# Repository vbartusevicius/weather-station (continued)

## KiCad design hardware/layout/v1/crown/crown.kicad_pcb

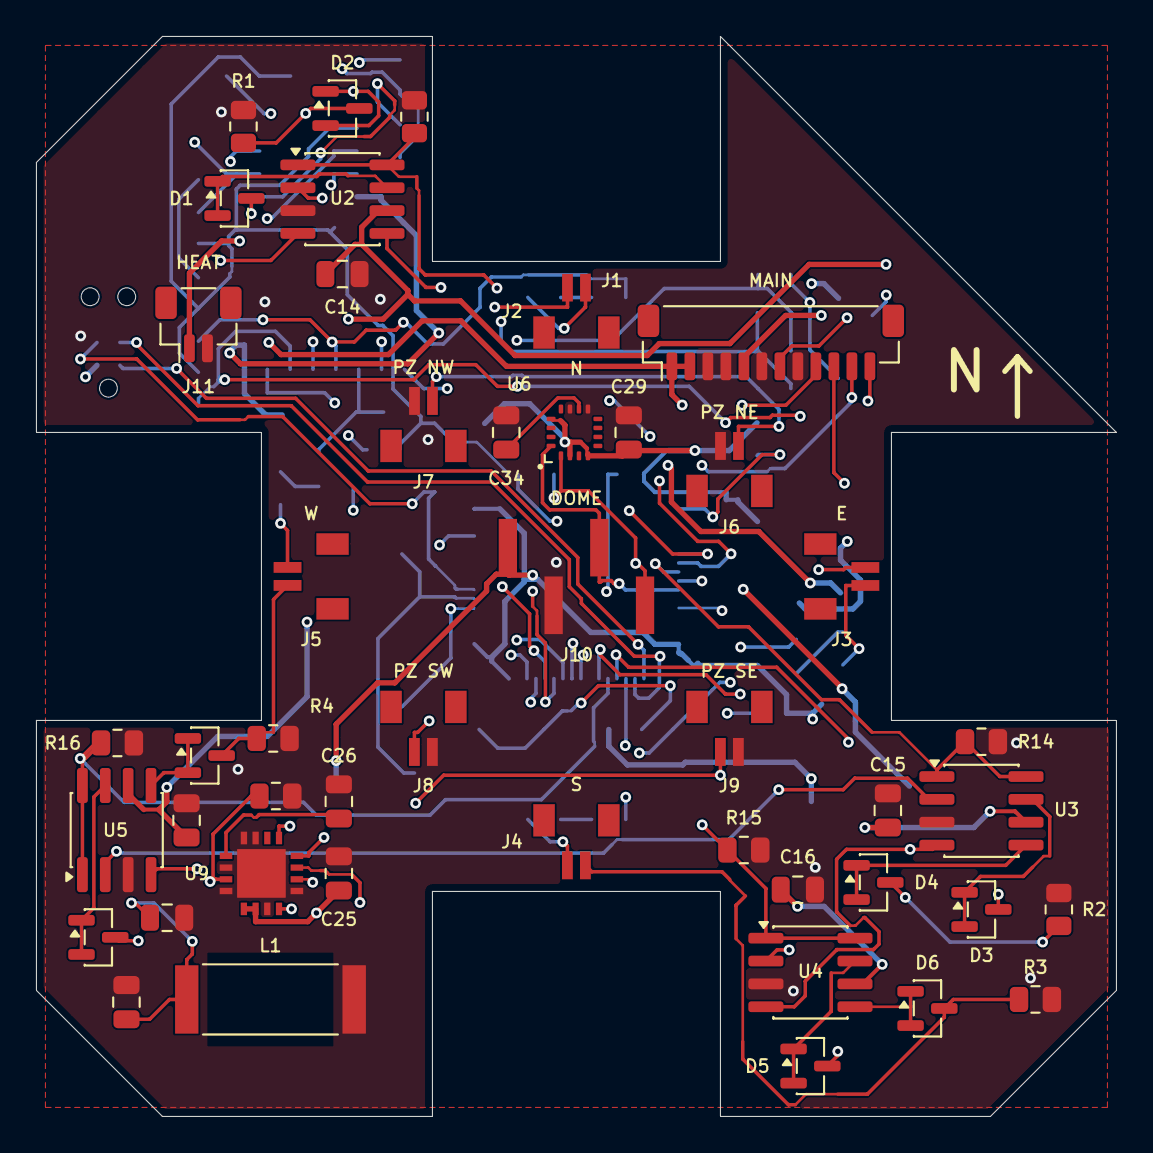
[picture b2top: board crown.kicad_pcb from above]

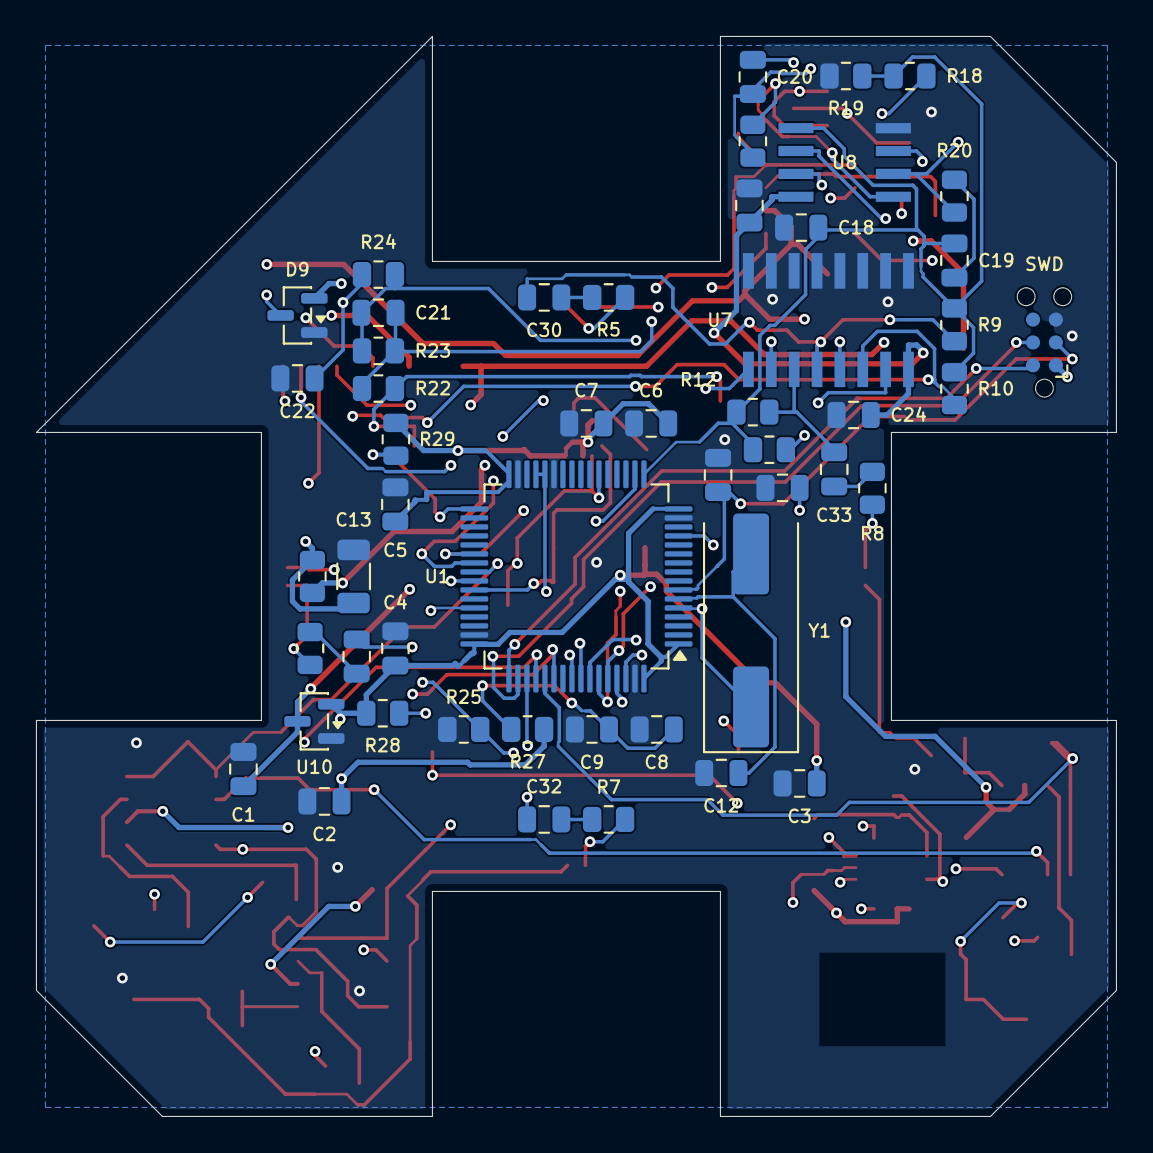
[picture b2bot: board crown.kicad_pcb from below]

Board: 4 copper layers, 60.0 x 60.0 mm, 96 parts (51 on the bottom side), 66 nets.

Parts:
C1, C8, C14, C15, C16, C17, C18, C25, C26: 1u 50V; C_0805_2012Metric
C2, C7, C34: 10u 10V; C_0805_2012Metric
C3, C4, C5, C6, C9, C10, C19, C23, C24, C29: 100n 50V; C_0805_2012Metric
C11, C12: 33p C0G 50V; C_0805_2012Metric
C13: 22u 25V; C_1206_3216Metric
C20: 220p C0G 50V; C_0805_2012Metric
C21: 22n 50V; C_0805_2012Metric
C22: 1n 50V; C_0805_2012Metric
C27, C28: 470p C0G 50V; C_0805_2012Metric
C30, C31, C32, C33: 10n 50V; C_0805_2012Metric
D1, D2, D3, D4, D5, D6, D7, D8, D9: BAV99; SOT-23
J1: Main board; JST_SH_BM12B-SRSS-TB_1x12-1MP_P1.00mm_Vertical
J2: XD_N; JST_BM02B-SRSS-TB
J3: XD_E; JST_BM02B-SRSS-TB
J4: XD_S; JST_BM02B-SRSS-TB
J5: XD_W; JST_BM02B-SRSS-TB
J6: PIEZO_NE; JST_BM02B-SRSS-TB
J7: PIEZO_NW; JST_BM02B-SRSS-TB
J8: PIEZO_SW; JST_BM02B-SRSS-TB
J9: PIEZO_SE; JST_BM02B-SRSS-TB
J10: DOME_SOCKET; HX_PZ2.54-1x4P-SMD
J11: AUX 12V_HEAT; JST_SH_BM02B-SRSS-TB_1x02-1MP_P1.00mm_Vertical
J12: SWD; Tag-Connect_TC2030-IDC-NL_2x03_P1.27mm_Vertical
L1: 100uH; AS3935_Antenna_MA5532_SDTR1103
R1, R2, R3, R4: 330R; R_0805_2012Metric
R5, R6, R7, R8: 47k; R_0805_2012Metric
R9, R10, R11, R12: 1M; R_0805_2012Metric
R13, R14, R15, R16: 4k7; R_0805_2012Metric
R17, R27: 10R; R_0805_2012Metric
R18, R19, R25, R26, R28, R29: 10k; R_0805_2012Metric
R20, R22: 1k; R_0805_2012Metric
R21: 6k8; R_0805_2012Metric
R23: 4M7; R_0805_2012Metric
R24: 22k; R_0805_2012Metric
U1: STM32G431RBT6; LQFP-64_10x10mm_P0.5mm
U2, U3, U4, U5: UCC27524ADR; SOIC-8_3.9x4.9mm_P1.27mm
U6: MMC5983MA; MEMSIC_MMC5983MA_LGA-16
U7: 74HC4052D; TI_CD4052BM96_SOIC-16
U8: TLV9062IDR; TI_TLV9062IDR_SOIC-8
U9: AS3935-BQFT; ScioSense_AS3935_QFN-16
U10: XC6206P332MR; SOT-23
Y1: 8MHz; Crystal_SMD_HC49-SD

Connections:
+3V3: C2.1, C3.1, C4.1, C5.1, C6.1, C7.1, C23.1, C24.1, C25.1, C29.1, D9.2, J10.1, J12.1, R27.1, R28.2, R29.2, U1.1, U1.16, U1.32, U1.48, U1.64, U6.2, U6.4, U6.13, U7.16, U8.8, U9.5, U9.6, U10.2
+3V3A: C8.1, C9.1, R18.1, R27.2, U1.28, U1.29
+5V: C1.1, J1.5, U10.3
+12V_HEAT: J1.1, J1.2, J11.1, R17.1
AS_ACG: C26.1, U9.1
AS_CS: U1.51, U9.8
AS_INP: C27.1, C28.1, L1.1, R26.1, U9.3
AS_IRQ: U1.62, U9.10
AS_MISO: U1.57, U9.12
AS_MOSI: U1.58, U9.13
AS_SCK: U1.56, U9.11
BL_PA10: R28.1, U1.44
BL_PB12: R29.1, U1.33
CROWN_BOOT0: J1.12, R25.1, U1.61
CROWN_IRQ: J1.10, U1.54
CROWN_NRST: C10.1, J1.11, J12.3, U1.7
GND: C1.2, C2.2, C3.2, C4.2, C5.2, C6.2, C7.2, C8.2, C9.2, C10.2, C11.2, C12.2, C13.2, C14.2, C15.2, C16.2, C17.2, C18.2, C22.2, C23.2, C24.2, C25.2, C26.2, C27.2, C28.2, C29.2, C34.2, D9.1, J1.3, J1.4, J1.6, J1.8, J6.2, J7.2, J8.2, J9.2, J10.2, J11.2, J12.5, L1.2, R1.2, R2.2, R3.2, R4.2, R13.2, R14.2, R15.2, R16.2, R19.2, R25.2, R26.2, U1.15, U1.27, U1.31, U1.47, U1.63, U2.3, U3.3, U4.3, U5.3, U6.9, U6.11, U7.1, U7.2, U7.3, U7.4, U7.5, U7.6, U7.7, U7.8, U8.4, U9.2, U9.4, U9.7, U9.9, U9.15, U9.16, U9.17, U10.1
I2C_SCL: J1.9, J10.4, U1.22, U6.1
I2C_SDA: J1.7, J10.3, U1.42, U6.16
MAG_CAP: C34.1, U6.10
MUX_S0: U1.59, U7.10
MUX_S1: U1.60, U7.9
PIEZO_IN: D9.3, J6.1, J7.1, J8.1, J9.1, R22.1
PIEZO_INV: C21.1, R22.2, R23.1, U8.6
PIEZO_OUT: C21.2, R23.2, R24.1, U8.7
RAIN_ADC: C22.1, R24.2, U1.18
SWCLK: J12.4, U1.50
SWDIO: J12.2, U1.49
TX_N: U1.52, U2.4, U3.4, U4.4, U5.4
TX_P: U1.38, U2.2, U3.2, U4.2, U5.2
US_AMP_FB: C20.1, R20.1, R21.1, U8.2
US_AMP_G: C19.1, R20.2
US_AMP_OUT: C20.2, R21.2, U1.13, U8.1
US_RX_MUX: U7.13, U8.3
US_VREF: C18.1, C19.2, R9.2, R10.2, R11.2, R12.2, R18.2, R19.1, U1.17, U8.5
VDRV: C13.1, C14.1, C15.1, C16.1, C17.1, R17.2, U2.6, U3.6, U4.6, U5.6
XD_EN_E: R14.1, U1.40, U3.1, U3.8
XD_EN_N: R13.1, U1.39, U2.1, U2.8
XD_EN_S: R15.1, U1.41, U4.1, U4.8
XD_EN_W: R16.1, U1.53, U5.1, U5.8
XD_E_A: D3.3, J3.1, R6.1
XD_E_B: D4.3, J3.2, R2.1
XD_E_OUT_A: D3.1, D3.2, U3.7
XD_E_OUT_B: D4.1, D4.2, U3.5
XD_E_RX: C31.2, R10.1, U7.14
XD_E_RXC: C31.1, R6.2
XD_N_A: D1.3, J2.1, R5.1
XD_N_B: D2.3, J2.2, R1.1
XD_N_OUT_A: D1.1, D1.2, U2.7
XD_N_OUT_B: D2.1, D2.2, U2.5
XD_N_RX: C30.2, R9.1, U7.12
XD_N_RXC: C30.1, R5.2
XD_S_A: D5.3, J4.1, R7.1
XD_S_B: D6.3, J4.2, R3.1
XD_S_OUT_A: D5.1, D5.2, U4.7
XD_S_OUT_B: D6.1, D6.2, U4.5
XD_S_RX: C32.2, R11.1, U7.15
XD_S_RXC: C32.1, R7.2
XD_W_A: D7.3, J5.1, R8.1
XD_W_B: D8.3, J5.2, R4.1
XD_W_OUT_A: D7.1, D7.2, U5.7
XD_W_OUT_B: D8.1, D8.2, U5.5
XD_W_RX: C33.2, R12.1, U7.11
XD_W_RXC: C33.1, R8.2
XTAL_IN: C11.1, U1.5, Y1.1
XTAL_OUT: C12.1, U1.6, Y1.2

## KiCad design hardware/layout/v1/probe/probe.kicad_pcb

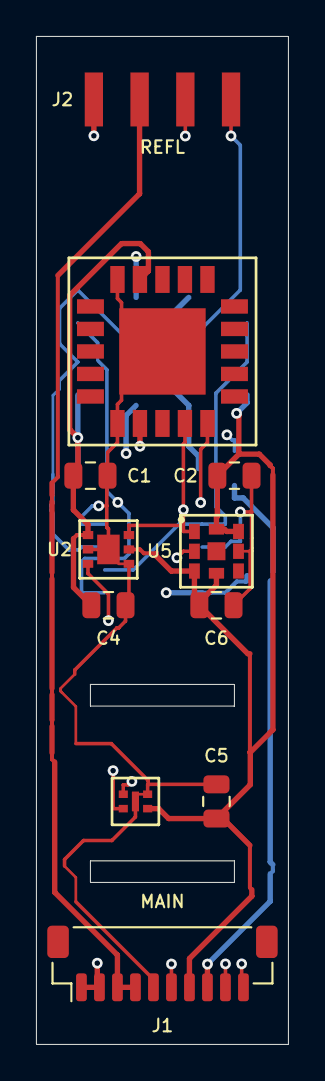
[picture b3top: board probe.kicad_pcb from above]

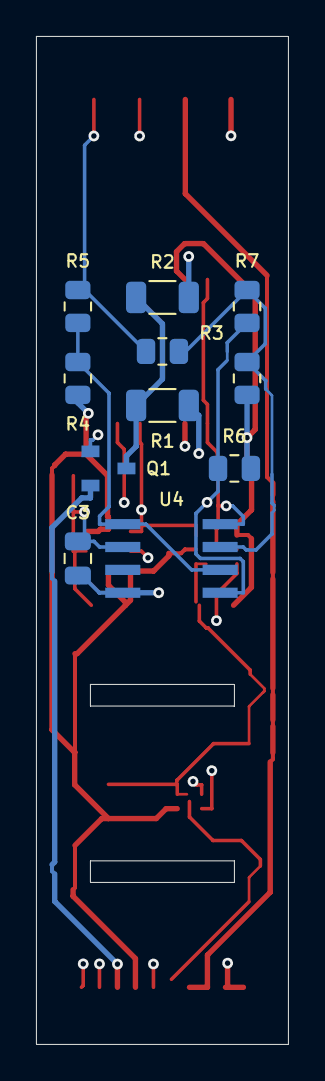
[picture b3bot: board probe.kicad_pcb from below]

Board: 4 copper layers, 14.0 x 56.0 mm, 22 parts (11 on the bottom side), 12 nets.

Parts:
C1: 10u 10V; C_0805_2012Metric
C2, C3, C4, C5, C6: 100n 50V; C_0805_2012Metric
J1: Main board; JST_SH_BM10B-SRSS-TB_1x10-1MP_P1.00mm_Vertical
J2: Reflector T-Socket SMD; HX_PM2.54-1x4P-RA-SMD
Q1: AO3400A; AOS_AO3400A_SOT-23
R1, R2: 680R; R_1206_3216Metric
R3, R4, R6: 10k; R_0805_2012Metric
R5: 51k; R_0805_2012Metric
R7: 470k; R_0805_2012Metric
TH1: 10k NTC; R_0805_2012Metric
U1: SCD41-D-R2; Sensirion_SCD41_LGA-20
U2: SGP41-D-R4; Sensirion_SGP41_DFN-6
U3: SHT40-AD1F-R2; Sensirion_SHT45_DFN-4
U4: LM2903DR2G; ON_LM393DR2G_SOIC-8
U5: BMP585; Bosch_BMP585_LGA-9

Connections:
+3V3_PROBE: C1.1, C2.1, C4.1, C5.1, C6.1, J1.7, R3.1, R4.1, R6.1, U1.7, U1.19, U2.1, U2.5, U3.3, U5.3, U5.4, U5.7, U5.8
+12V_HEAT: C3.1, J1.1, J1.2, J2.1, R1.1, R2.1, U4.8
CO2_GATE: Q1.1, R6.2, R7.1, U4.1
CO2_HEAT_RTN: J1.8, Q1.2
CO2_HEAT_SW: Q1.3, R1.2, R2.2
CO2_NTC: R3.2, R7.2, TH1.1, U4.3
CO2_VSET: R4.2, R5.1, U4.2, U4.5
GND: C1.2, C2.2, C3.2, C4.2, C5.2, C6.2, J1.5, J2.4, R5.2, TH1.2, U1.6, U1.20, U1.21, U2.2, U2.4, U2.7, U3.4, U3.5, U4.4, U4.6, U5.6
HEAT_SW: J1.3, J1.4, J2.2
I2C_SCL: J1.10, U1.9, U2.6, U3.2, U5.1
I2C_SDA: J1.9, U1.10, U2.3, U3.1, U5.2
NTC_SENSE: J1.6, J2.3

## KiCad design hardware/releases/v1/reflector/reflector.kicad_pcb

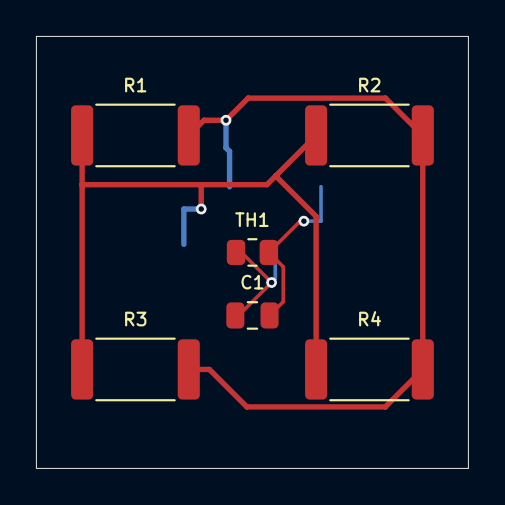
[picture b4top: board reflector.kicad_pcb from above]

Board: 4 copper layers, 24.0 x 24.0 mm, 7 parts (1 on the bottom side), 4 nets.

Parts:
C1: 100n 50V; C_0805_2012Metric
J1: Probe T-Header SMD; HX_PZ2.54-1x4P-SMD
R1, R2, R3, R4: 120R; R_2512_6332Metric
TH1: 10k NTC; R_0805_2012Metric

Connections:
+12V_HEAT: J1.1, R1.1, R2.1, R3.1, R4.1
GND: C1.2, J1.4, TH1.2
HEAT_SW: J1.2, R1.2, R2.2, R3.2, R4.2
NTC_SENSE: C1.1, J1.3, TH1.1

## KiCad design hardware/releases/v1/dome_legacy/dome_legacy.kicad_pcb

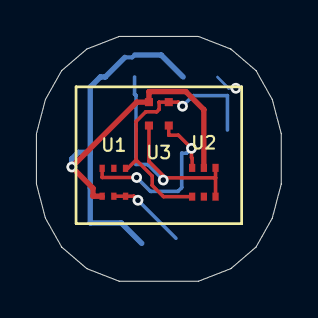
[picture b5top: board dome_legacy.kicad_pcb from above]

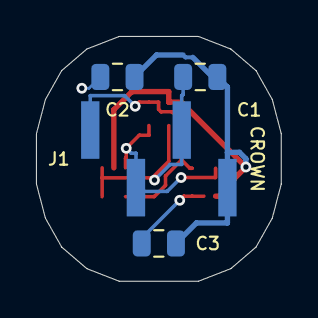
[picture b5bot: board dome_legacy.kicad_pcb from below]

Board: 4 copper layers, 13.6 x 13.6 mm, 7 parts (4 on the bottom side), 4 nets.

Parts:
C1, C2: 100n 50V; C_0805_2012Metric
C3: 1u 50V; C_0805_2012Metric
J1: CROWN_RISER; HX_PZ2.54-1x4P-SMD
U1: LTR-390UV-01; LiteOn_LTR-390UV-01
U2: TSL25911FN; AMS_TSL25911FN
U3: GUVB-C31SM; GenUV_GUVB-C31SM

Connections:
+3V3: C1.1, C2.1, C3.1, J1.1, U1.1, U2.5, U3.4
GND: C1.2, C2.2, C3.2, J1.2, U1.2, U1.3, U2.3, U2.4, U3.1
I2C_SCL: J1.4, U1.4, U2.1, U3.3
I2C_SDA: J1.3, U1.6, U2.6, U3.2

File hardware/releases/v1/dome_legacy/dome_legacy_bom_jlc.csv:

Comment,Designator,Footprint,LCSC Part #
100n 50V,"C1,C2",C_0805_2012Metric,C49678
1u 50V,C3,C_0805_2012Metric,C28323
CROWN_RISER,J1,HX_PZ2.54-1x4P-SMD,C41417361
LTR-390UV-01,U1,LiteOn_LTR-390UV-01,C492374
TSL25911FN,U2,AMS_TSL25911FN,C176812

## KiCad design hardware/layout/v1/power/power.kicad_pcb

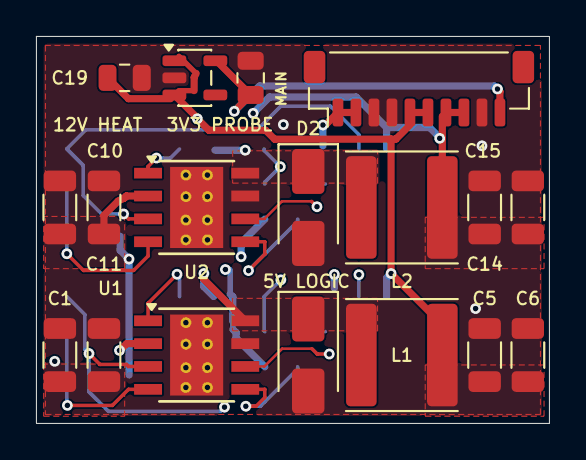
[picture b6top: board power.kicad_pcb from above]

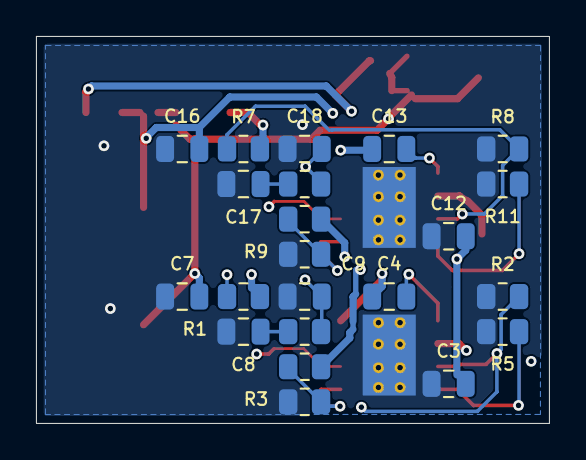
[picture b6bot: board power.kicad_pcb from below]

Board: 4 copper layers, 28.5 x 21.5 mm, 40 parts (22 on the bottom side), 19 nets.

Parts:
C1, C2, C10, C11: 2u2 100V; C_1206_3216Metric
C3, C12: 100n 100V; C_0805_2012Metric
C4, C7, C13, C16: 100n 50V; C_0805_2012Metric
C5, C6: 47u 10V; C_1206_3216Metric
C8: 33n 50V; C_0805_2012Metric
C9, C18: 68p C0G 50V; C_0805_2012Metric
C14, C15: 22u 25V; C_1206_3216Metric
C17: 18n 50V; C_0805_2012Metric
C19: 1u 50V; C_0805_2012Metric
C20: 10u 10V; C_0805_2012Metric
D1, D2: B360A; D_SMA
J1: Main board; JST_SH_BM10B-SRSS-TB_1x10-1MP_P1.00mm_Vertical
L1: 8.2uH; L_Sunlord_SWPA6045S
L2: 22uH; L_Sunlord_SWPA6045S
R1, R7: 511k; R_0805_2012Metric
R2, R8: 82k5; R_0805_2012Metric
R3: 53k6; R_0805_2012Metric
R4: 10k2; R_0805_2012Metric
R5, R11: 130k; R_0805_2012Metric
R6, R12: 6k49; R_0805_2012Metric
R9: 140k; R_0805_2012Metric
R10: 10k; R_0805_2012Metric
U1, U2: TPS54360DDAR; TI_SO-PowerPAD-8_ThermalVias
U3: AP2112K-3.3; SOT-23-5

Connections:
+3V3_PROBE: C20.1, J1.10, U3.5
+5V: C5.1, C6.1, C7.1, C19.1, J1.5, J1.6, L1.2, R3.1, U3.1, U3.3
+12V_HEAT: C14.1, C15.1, C16.1, J1.7, J1.8, L2.2, R9.1
GND: C1.2, C2.2, C3.2, C5.2, C6.2, C7.2, C8.2, C9.2, C10.2, C11.2, C12.2, C14.2, C15.2, C16.2, C17.2, C18.2, C19.2, C20.2, D1.2, D2.2, J1.3, J1.4, J1.9, R2.2, R4.2, R5.2, R8.2, R10.2, R11.2, U1.7, U1.9, U2.7, U2.9, U3.2
HEAT_BST: C13.1, U2.1
HEAT_CC: C17.1, R12.2
HEAT_COMP: C18.1, R12.1, U2.6
HEAT_EN: R7.2, R8.1, U2.3
HEAT_FB: R9.2, R10.1, U2.5
HEAT_RT: R11.1, U2.4
HEAT_SW: C13.2, D2.1, L2.1, U2.8
LOGIC_BST: C4.1, U1.1
LOGIC_CC: C8.1, R6.2
LOGIC_COMP: C9.1, R6.1, U1.6
LOGIC_EN: R1.2, R2.1, U1.3
LOGIC_FB: R3.2, R4.1, U1.5
LOGIC_RT: R5.1, U1.4
LOGIC_SW: C4.2, D1.1, L1.1, U1.8
VIN_PROT: C1.1, C2.1, C3.1, C10.1, C11.1, C12.1, J1.1, J1.2, R1.1, R7.1, U1.2, U2.2

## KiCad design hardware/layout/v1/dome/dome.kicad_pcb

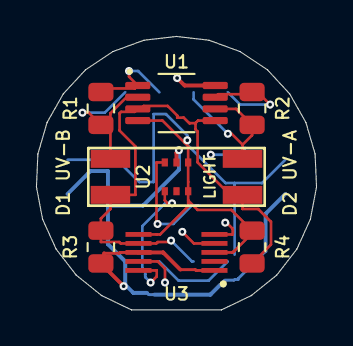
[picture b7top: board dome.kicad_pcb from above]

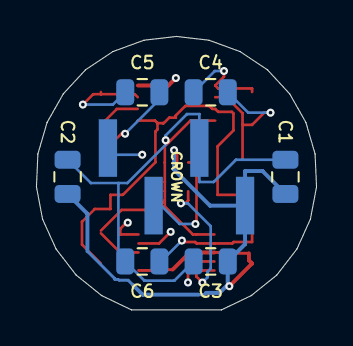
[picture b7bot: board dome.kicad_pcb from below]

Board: 4 copper layers, 15.6 x 15.2 mm, 16 parts (7 on the bottom side), 9 nets.

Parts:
C1, C2, C3: 100n 50V; C_0805_2012Metric
C4: 10n 50V; C_0805_2012Metric
C5: 22n 50V; C_0805_2012Metric
C6: 1u 50V; C_0805_2012Metric
D1: GUVB-C21SD; Genicom_COB2418
D2: GUVA-C22SD; Genicom_COB2418
J1: CROWN_RISER; HX_PZ2.54-1x4P-SMD
R1: 10M; R_0805_2012Metric
R2: 4M7; R_0805_2012Metric
R3: 100k; R_0805_2012Metric
R4: 10k; R_0805_2012Metric
U1: TLV9062IDGKR; TI_TLV9062_VSSOP-8
U2: TSL25911FN; AMS_TSL25911FN
U3: ADS1115IDGSR; TI_ADS1115_VSSOP-10

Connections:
+3V3: C1.1, C2.1, C3.1, J1.1, R3.1, U1.8, U2.5, U3.1, U3.8
GND: C1.2, C2.2, C3.2, C6.2, J1.2, R4.2, U1.4, U2.3, U2.4, U3.3, U3.6
I2C_SCL: J1.4, U2.1, U3.10
I2C_SDA: J1.3, U2.6, U3.9
UVA_IN: C5.1, D2.2, R2.1, U1.6
UVA_OUT: C5.2, R2.2, U1.7, U3.5
UVB_IN: C4.1, D1.2, R1.1, U1.2
UVB_OUT: C4.2, R1.2, U1.1, U3.4
UV_VB: C6.1, D1.1, D2.1, R3.2, R4.1, U1.3, U1.5, U3.7

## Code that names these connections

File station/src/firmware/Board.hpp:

#pragma once

#include <cstddef>
#include <cstdint>

#include "EspIdfHostStubs.hpp"

// Seeed XIAO ESP32-C6 pin assignment on AeroMet V1 main board:
//   D0  / GPIO0  = VIN_ADC    (ADC1_CH0: 12-32 V supply monitor via 100k/10k divider)
//   D1  / GPIO1  = NTC_SENSE  (ADC1_CH1: reflector 10k NTC thermistor + SW1 SERVICE button)
//   D2  / GPIO2  = CROWN_BOOT0 (crown STM32 BOOT0: high + reset = ROM I2C bootloader)
//   D3  / GPIO21 = HEAT_PWM   (LEDC PWM driving AO3400A reflector de-icing heater MOSFET)
//   D4  / GPIO22 = I2C_SDA    (crown STM32 0x2A, BMP585, LSM6DS3, ADS1115, PMSA003I, SHT40, SGP41, SCD41, LTR390,
//                              TSL25911, GUVB-C31SM, MMC5983MA)
//   D5  / GPIO23 = I2C_SCL    (I2C clock, 100 kHz standard mode for every device)
//   D6  / GPIO16 = RS485_TX   (UART1 TX -> SP3485 DI)
//   D7  / GPIO17 = RS485_RX   (UART1 RX <- SP3485 RO)
//   D8  / GPIO19 = RS485_DE   (UART1 RTS in RS-485 half-duplex mode -> SP3485 DE + /RE)
//   D9  / GPIO20 = CROWN_IRQ  (crown data-ready / lightning interrupt, input)
//   D10 / GPIO18 = CROWN_NRST (crown STM32 reset, open-drain)
// Wind, rain and lightning are measured by the crown STM32 (shared/include/crown_protocol.hpp).
namespace station {
namespace firmware {
namespace board {

constexpr gpio_num_t fab_sw_pin = GPIO_NUM_9;

constexpr gpio_num_t vin_adc_pin = GPIO_NUM_0;
constexpr adc_channel_t vin_adc_channel = ADC_CHANNEL_0;

constexpr gpio_num_t ntc_sense_pin = GPIO_NUM_1;
constexpr adc_channel_t ntc_adc_channel = ADC_CHANNEL_1;

constexpr gpio_num_t crown_boot0_pin = GPIO_NUM_2;
constexpr gpio_num_t heat_pwm_pin = GPIO_NUM_21;
constexpr gpio_num_t i2c_sda_pin = GPIO_NUM_22;
constexpr gpio_num_t i2c_scl_pin = GPIO_NUM_23;
constexpr gpio_num_t rs485_tx_pin = GPIO_NUM_16;
constexpr gpio_num_t rs485_rx_pin = GPIO_NUM_17;
constexpr gpio_num_t rs485_de_pin = GPIO_NUM_19;
constexpr gpio_num_t crown_irq_pin = GPIO_NUM_20;
constexpr gpio_num_t crown_nrst_pin = GPIO_NUM_18;

// Seeed XIAO ESP32-C6 internal FM8625H SPDT RF switch pins (selects onboard U.FL / IPEX external antenna):
//   GPIO3  = RF_SW_PWR (LOW = enables FM8625H RF switch VDD)
//   GPIO14 = ANT_SEL   (HIGH = routes RF to external U.FL horizontal FPC dipole; LOW = internal chip antenna)
constexpr gpio_num_t rf_switch_power_pin = GPIO_NUM_3;
constexpr gpio_num_t rf_antenna_select_pin = GPIO_NUM_14;
constexpr std::int8_t wifi_max_tx_power_quarter_dbm = 82;  // 82 * 0.25 dBm = +20.5 dBm (112 mW max linear PA)

// I2C 7-bit addresses of all onboard & probe/crown/dome sensors
constexpr std::uint8_t i2c_addr_mmc5983 = 0x30;  // crown U6 MEMSIC MMC5983MA 18-bit AMR compass
constexpr std::uint8_t i2c_addr_tsl25911 = 0x29;
constexpr std::uint8_t i2c_addr_guvb_c31sm = 0x39;  // dome U3 GenUV GUVB-C31SM AlGaN UV-B sensor
constexpr std::uint8_t i2c_addr_sht4x = 0x44;   // probe U3 SHT40-AD1F (SHT4x command set)
constexpr std::uint8_t i2c_addr_bmp581 = 0x47;  // probe U5 BMP585 (BMP581 register map, chip ID 0x51)
constexpr std::uint8_t i2c_addr_ltr390 = 0x53;
constexpr std::uint8_t i2c_addr_sgp41 = 0x59;   // probe U2
constexpr std::uint8_t i2c_addr_scd41 = 0x62;
constexpr std::uint8_t i2c_addr_pmsa003i = 0x12;  // Plantower PMSA003I in the base pod via main J4 (100 kHz)
constexpr std::uint8_t i2c_addr_lsm6ds3 = 0x6A;
constexpr std::uint8_t i2c_addr_ads1115 = 0x48;  // main U4 heater power monitor
constexpr std::uint8_t i2c_addr_dome_adc = 0x49;  // photodiode dome U3 ADS1115 (UV-B / UV-A transimpedance outputs)
constexpr float refl_shunt_ohm = 0.1F;    // main R16 (reflector heater return)
constexpr float probe_shunt_ohm = 1.0F;   // main R17 (probe heater return, CO2_HEAT_RTN)
constexpr float rail5_divider = 2.0F;     // main R24/R25 (+5V electronics rail), 10k/10k
constexpr float rail_heat_divider = 4.0F; // main R20/R21 (+12V_HEAT heater rail), 30k/10k

// 100 kHz for the whole bus: ~180 pF (12 devices + 260 / 60 mm cables) with 2.2k pull-ups rises in ~335 ns, over
// the 300 ns fast-mode limit but 3x inside the 1000 ns standard-mode one. Bus load ~35 % (IMU 200 Hz, BMP585 FIFO
// 100 Hz, crown 4 quads/s, slow sensors).
constexpr std::uint32_t i2c_speed_hz = 100000;

constexpr bool usb_pin(gpio_num_t pin) {
    return pin == GPIO_NUM_12 || pin == GPIO_NUM_13;
}

constexpr bool pins_distinct() {
    const gpio_num_t pins[] = {
        vin_adc_pin, ntc_sense_pin, crown_boot0_pin, heat_pwm_pin,
        i2c_sda_pin, i2c_scl_pin,   rs485_tx_pin,    rs485_rx_pin,
        rs485_de_pin, crown_irq_pin, crown_nrst_pin,
        rf_switch_power_pin,        rf_antenna_select_pin,
    };
    for (std::size_t i = 0; i < sizeof(pins) / sizeof(pins[0]); ++i) {
        if (usb_pin(pins[i])) {
            return false;
        }
        for (std::size_t j = i + 1; j < sizeof(pins) / sizeof(pins[0]); ++j) {
            if (pins[i] == pins[j]) {
                return false;
            }
        }
    }
    return true;
}

static_assert(pins_distinct(), "AeroMet V1 pins must be distinct and avoid USB D-/D+ (GPIO12/13)");

}  // namespace board
}  // namespace firmware
}  // namespace station

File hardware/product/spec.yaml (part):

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    poles: 4
    pitch: 3.5
    type: push-in-spring (Cixi Kefa KF250-3.5-4P-1, C475156)
    labels: [VIN_12_32V, GND, RS485_A, RS485_B]
  pm_sensor:
    board: main
    poles: 6
    pitch: 1.5
    type: jst-zh-smd (JST B6B-ZR-SM4-TF -> harness -> Plantower PMSA003I 2x5 1.27 mm)
    labels: [+5V, GND, I2C_SDA, I2C_SCL, NC, NC]

checks:
  component_air_gap: 1.5
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
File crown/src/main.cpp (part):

// Crown v2 firmware (STM32G431RBT6): ultrasonic wind, piezo rain and AS3935 lightning as an I2C peripheral of main.
//
// Hardware (hardware/circuits/blocks/crown_sensors.py):
//   TIM8 CH1 / CH1N (PC6 / PC10) -> UCC27524 INA / INB of all four drivers; XD_EN_N/E/S/W (PC7, PC8, PC9, PC11)
//   select the transmitting transducer. MUX_S0/S1 (PB6, PB7) select the listening one on the 74HC4052.
//   PA1 -> OPAMP1 PGA (x2..x32, biased at VREF through PA3 = VINM0) -> ADC1 (internal VOPAMP1), triggered at exactly
//   2 MSPS by TIM6, DMA1 CH1.
//   PA4 -> ADC2_IN17 rain charge amplifier, 50 kSPS by TIM7, circular DMA1 CH2.
//   SPI1 (PB3 SCK, PB4 MISO, PB5 MOSI, PA15 CS) + PB9 IRQ -> AS3935.
//   I2C2 (PC4 SCL, PA8 SDA) peripheral 0x2A; PC12 = CROWN_IRQ to main. HSE 8 MHz -> 170 MHz.
// The DSP / protocol logic lives in lib/crown_core (host-tested: pio test -d crown -e native).

#include <cstring>
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namespace {

constexpr crown::FirmwareVersion kVersion{0, 3, 0};   // 0.3: PGA biased at VREF, burst end fix, rain blanking
// OPAMP1 PGA "inverting input used as bias" (VINM0 = PA3 = US_VREF): Vout = G (Vin - VREF) + VREF. These bits live in
// the PGGAIN field together with the gain, so every gain change must keep them.
constexpr std::uint32_t kPgaConnect = OPAMP_PGA_CONNECT_INVERTINGINPUT_IO0_BIAS;
constexpr std::uint32_t kRainBlankTailSamples = 50;   // 1 ms ring-down after the capture (50 kSPS)
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    hopamp1.Init.NonInvertingInput = OPAMP_NONINVERTINGINPUT_IO0;   // PA1
    hopamp1.Init.InternalOutput = ENABLE;
    hopamp1.Init.TimerControlledMuxmode = OPAMP_TIMERCONTROLLEDMUXMODE_DISABLE;
    hopamp1.Init.PgaConnect = kPgaConnect;                          // PA3 = US_VREF
    hopamp1.Init.PgaGain = OPAMP_PGA_GAIN_4_OR_MINUS_3;
    hopamp1.Init.UserTrimming = OPAMP_TRIMMING_FACTORY;
    if (HAL_OPAMP_Init(&hopamp1) != HAL_OK) error_loop();
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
